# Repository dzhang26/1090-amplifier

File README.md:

# 1090-amplifier
Pre-amplifier for the 1.09 GHz mode-A/C/S / ADS-B receiver

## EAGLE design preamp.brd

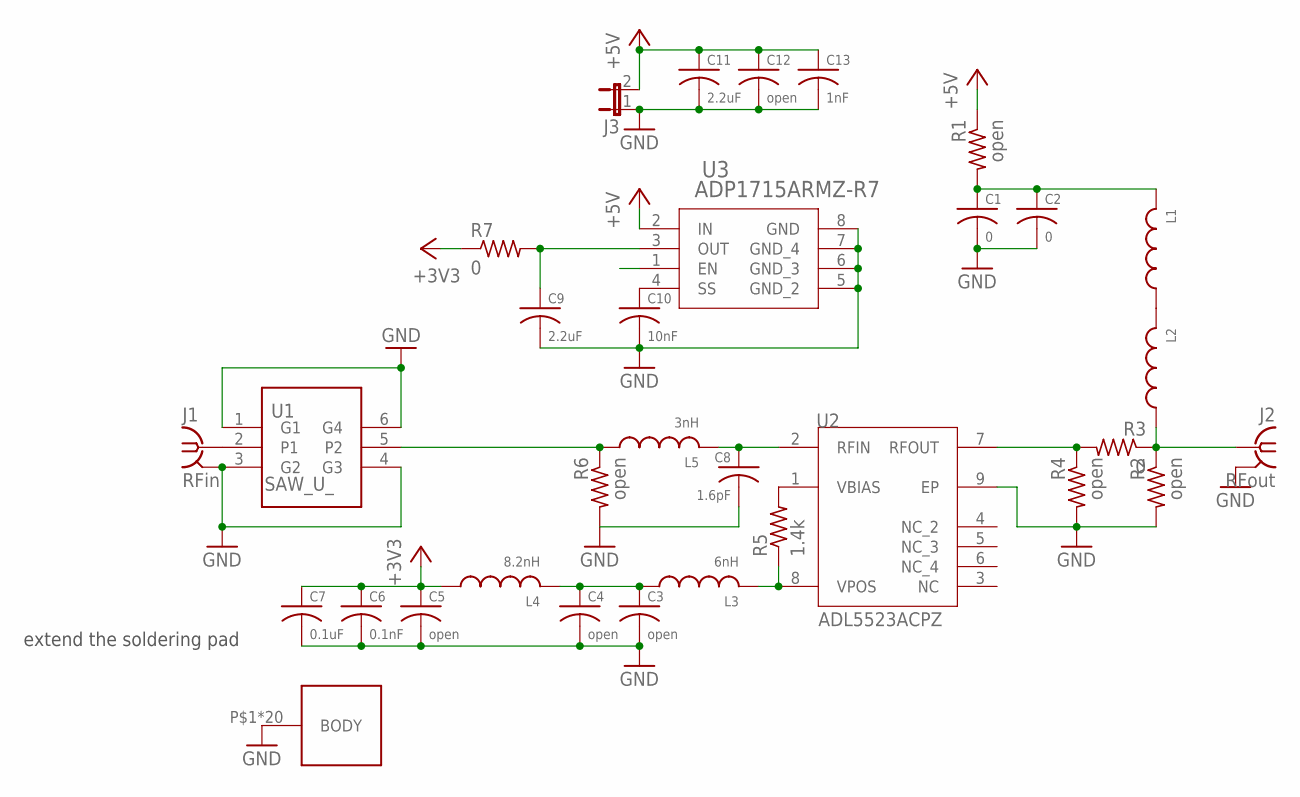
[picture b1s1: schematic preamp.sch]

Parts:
C1, C2: 0; C0603
C3, C4, C5, C12: open; C0603
C6: 0.1nF; C0603
C7: 0.1uF; C0603
C8: 1.6pF; C0603
C9, C11: 2.2uF; C0603
C10: 10nF; C0603
C13: 1nF; C0603
J1: RFin; J502-ND-142-0711-821/826; MPN 142-0711-821
J2: RFout; J502-ND-142-0711-821/826; MPN 142-0711-821
J3: JP1E; JP1
L1, L2: L-USL0603; L0603
L3: 6nH; L0603
L4: 8.2nH; L0603
L5: 3nH; L0603
R1, R2, R4, R6: open; R0603
R3, R7: 0; R0603
R5: 1.4k; R0603
U1: SAW_U_; SAW_U
U2: ADL5523ACPZ; CP8-2_DZ
U3: ADP1715ARMZ-R7; RM_8
U10: BMI-S-X03

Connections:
+3V3: C5.1, C6.1, C7.1, L4.1, R7.1
+5V: C11.1, C12.1, C13.1, J3.2, R1.1, U3.1 (EN), U3.2 (IN)
ADP1715_3: C9.1, R7.2, U3.3 (OUT)
GND: C1.2, C2.2, C3.2, C4.2, C5.2, C6.2, C7.2, C8.2, C9.2, C10.2, C11.2, C12.2, C13.2, J1.G@1 (GND), J1.G@2 (GND), J1.G@3 (GND), J1.G@4 (GND), J2.G@1 (GND), J2.G@2 (GND), J2.G@3 (GND), J2.G@4 (GND), J3.1, R2.2, R4.2, R6.2, U1.1 (G1), U1.3 (G2), U1.4 (G3), U1.6 (G4), U2.9 (EP), U3.5 (GND_2), U3.6 (GND_3), U3.7 (GND_4), U3.8 (GND), U10.P$1, U10.P$2, U10.P$3, U10.P$4, U10.P$5, U10.P$6, U10.P$7, U10.P$8, U10.P$10, U10.P$11, U10.P$12, U10.P$13, U10.P$14, U10.P$15, U10.P$16, U10.P$17, U10.P$18, U10.P$19, U10.P$20, U10.P$21
unnamed: L1.1, L2.2
unnamed: R5.2, U2.1 (VBIAS)
unnamed: C1.1, C2.1, L1.2, R1.2
unnamed: J1.1, U1.2 (P1)
unnamed: C3.1, C4.1, L3.1, L4.2
unnamed: C8.1, L5.2, U2.2 (RFIN)
unnamed: L5.1, R6.1, U1.5 (P2)
unnamed: L3.2, R5.1, U2.8 (VPOS)
unnamed: C10.1, U3.4 (SS)
unnamed: R3.2, R4.1, U2.7 (RFOUT)
unnamed: J2.1, L2.1, R2.1, R3.1

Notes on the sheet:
extend the soldering pad

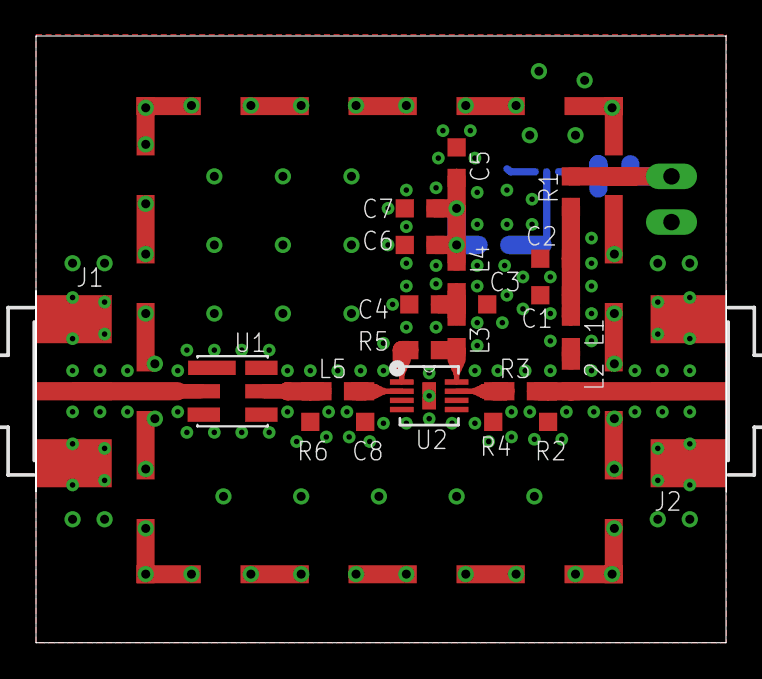
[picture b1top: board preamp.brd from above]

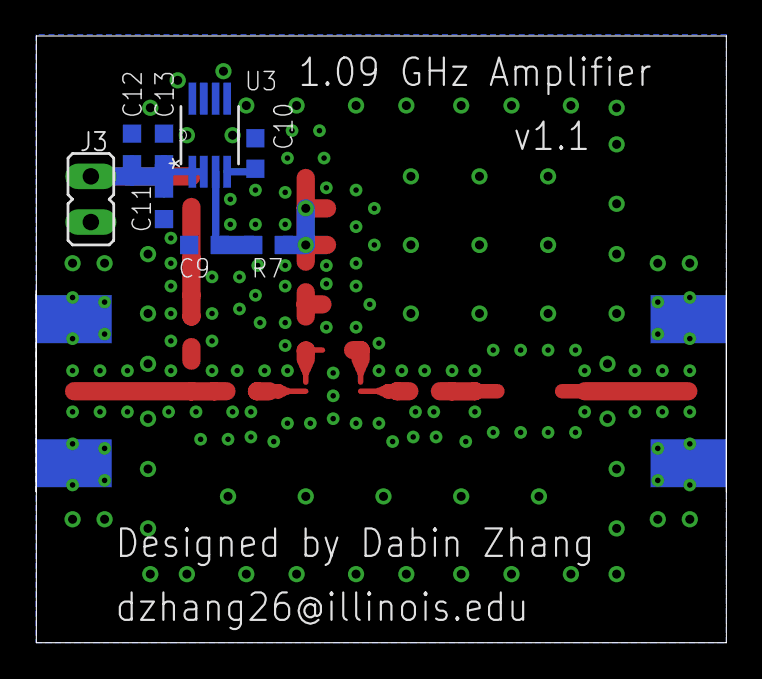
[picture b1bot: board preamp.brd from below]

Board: 2 copper layers, 38.4 x 33.7 mm, 32 parts (8 on the bottom side), 15 nets.

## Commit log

2015-05-06 Fabricated version 2
